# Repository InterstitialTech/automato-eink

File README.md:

# automato-eink
eink display module adapter for automato ecosystem

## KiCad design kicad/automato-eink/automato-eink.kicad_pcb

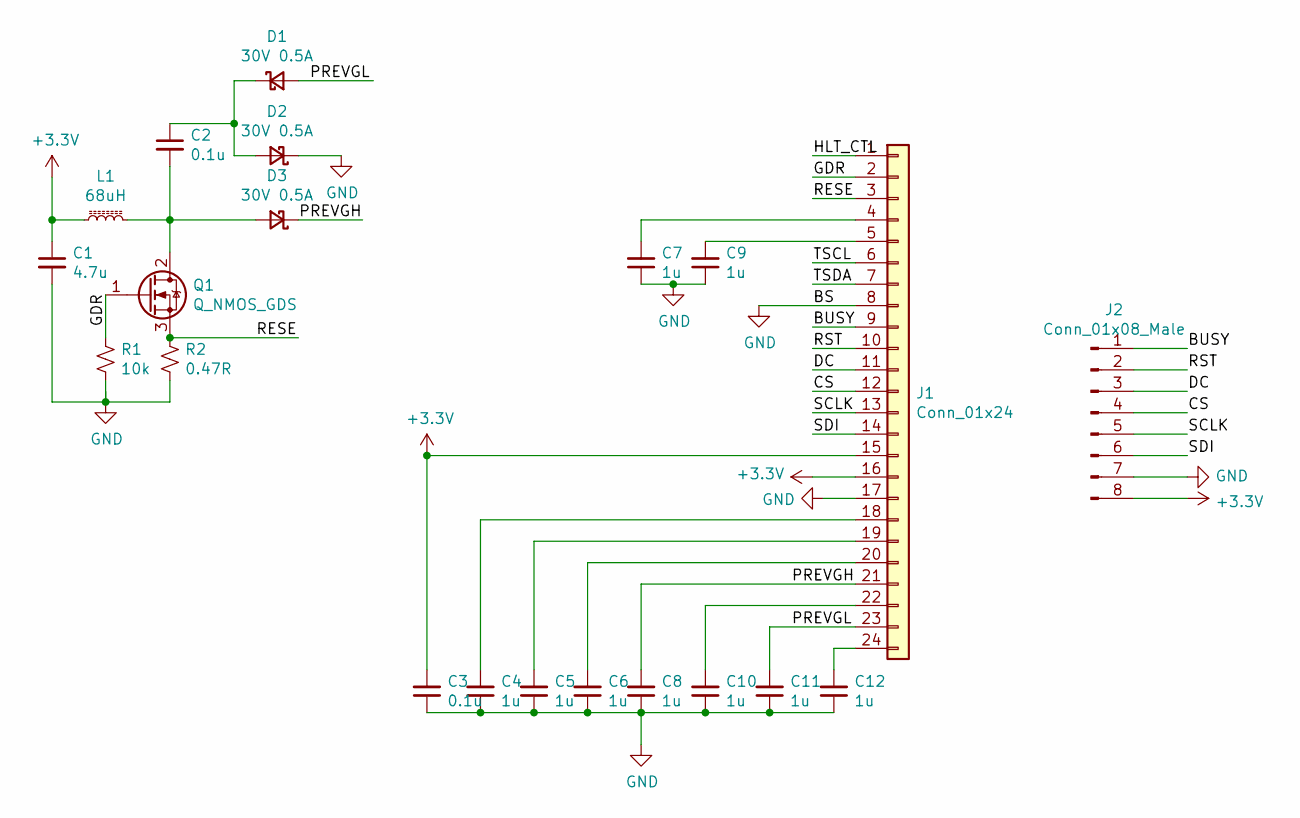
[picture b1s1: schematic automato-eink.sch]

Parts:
C1: 4.7u; C_0805_2012Metric
C2, C3: 0.1u; C_0805_2012Metric
C4, C5, C6, C7, C8, C9, C10, C11, C12: 1u; C_0805_2012Metric
D1, D2, D3: 30V 0.5A; D_SOD-123F
J1: Conn_01x24; Hirose_FH12-24S-0.5SH_1x24-1MP_P0.50mm_Horizontal
J2: Conn_01x08_Male; PinHeader_1x08_P2.54mm_Vertical
L1: 68uH; L_7.3x7.3_H3.5
Q1: Q_NMOS_GDS; SOT-23
R1: 10k; R_0805_2012Metric
R2: 0.47R; R_0805_2012Metric

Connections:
+3V3: C1.1, C3.2, J1.15, J1.16, J2.8, L1.1
/BUSY: J1.9, J2.1
/CS: J1.12, J2.4
/DC: J1.11, J2.3
/GDR: J1.2, Q1.1 (G), R1.1
/HLT_CTL: J1.1
/PREVGH: C8.2, D3.1 (K), J1.21
/PREVGL: C11.2, D1.2 (A), J1.23
/RESE: J1.3, Q1.3 (S), R2.1
/RST: J1.10, J2.2
/SCLK: J1.13, J2.5
/SDI: J1.14, J2.6
/TSCL: J1.6
/TSDA: J1.7
GND: C1.2, C3.1, C4.1, C5.1, C6.1, C7.1, C8.1, C9.1, C10.1, C11.1, C12.1, D2.1 (K), J1.8, J1.17, J2.7, R1.2, R2.2
unnamed: C2.1, D1.1 (K), D2.2 (A)
unnamed: C2.2, D3.2 (A), L1.2, Q1.2 (D)
unnamed: C4.2, J1.18
unnamed: C5.2, J1.19
unnamed: C6.2, J1.20
unnamed: C7.2, J1.4
unnamed: C9.2, J1.5
unnamed: C10.2, J1.22
unnamed: C12.2, J1.24

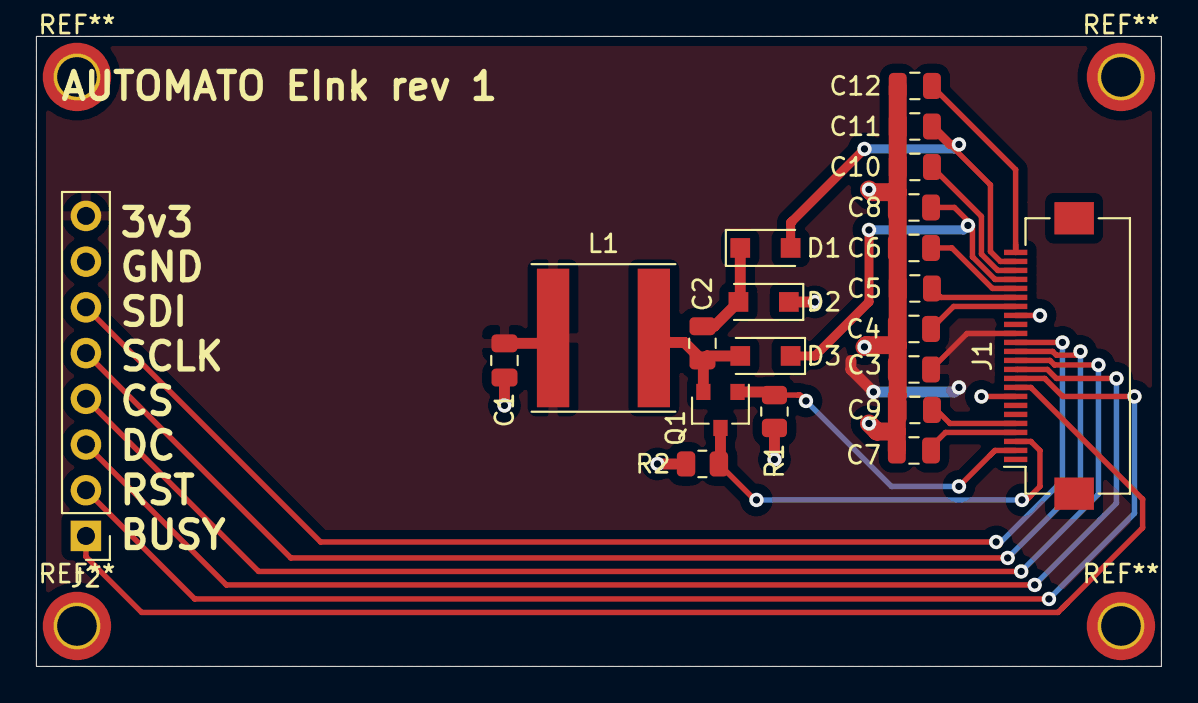
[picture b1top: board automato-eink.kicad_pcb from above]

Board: 2 copper layers, 62.5 x 35.0 mm, 21 parts (0 on the bottom side), 21 nets.

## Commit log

2022-07-18 add license
2022-07-18 add parts and begin schematic capture
    reference: https://www.waveshare.com/w/upload/7/7e/ESP8266_e-paper.pdf
2022-07-19 finish schematic capture
2022-07-19 added footprints
2022-07-19 add pcb
2022-07-19 first route
2022-07-20 update inductor, add stand-offs
2022-07-20 add bom
2022-07-21 annotate and place components
2022-07-21 add inductor footprint
2022-07-21 viewing more layers
2022-07-21 Update automato-eink.kicad_pcb-bak
2022-08-17 add standoffs
